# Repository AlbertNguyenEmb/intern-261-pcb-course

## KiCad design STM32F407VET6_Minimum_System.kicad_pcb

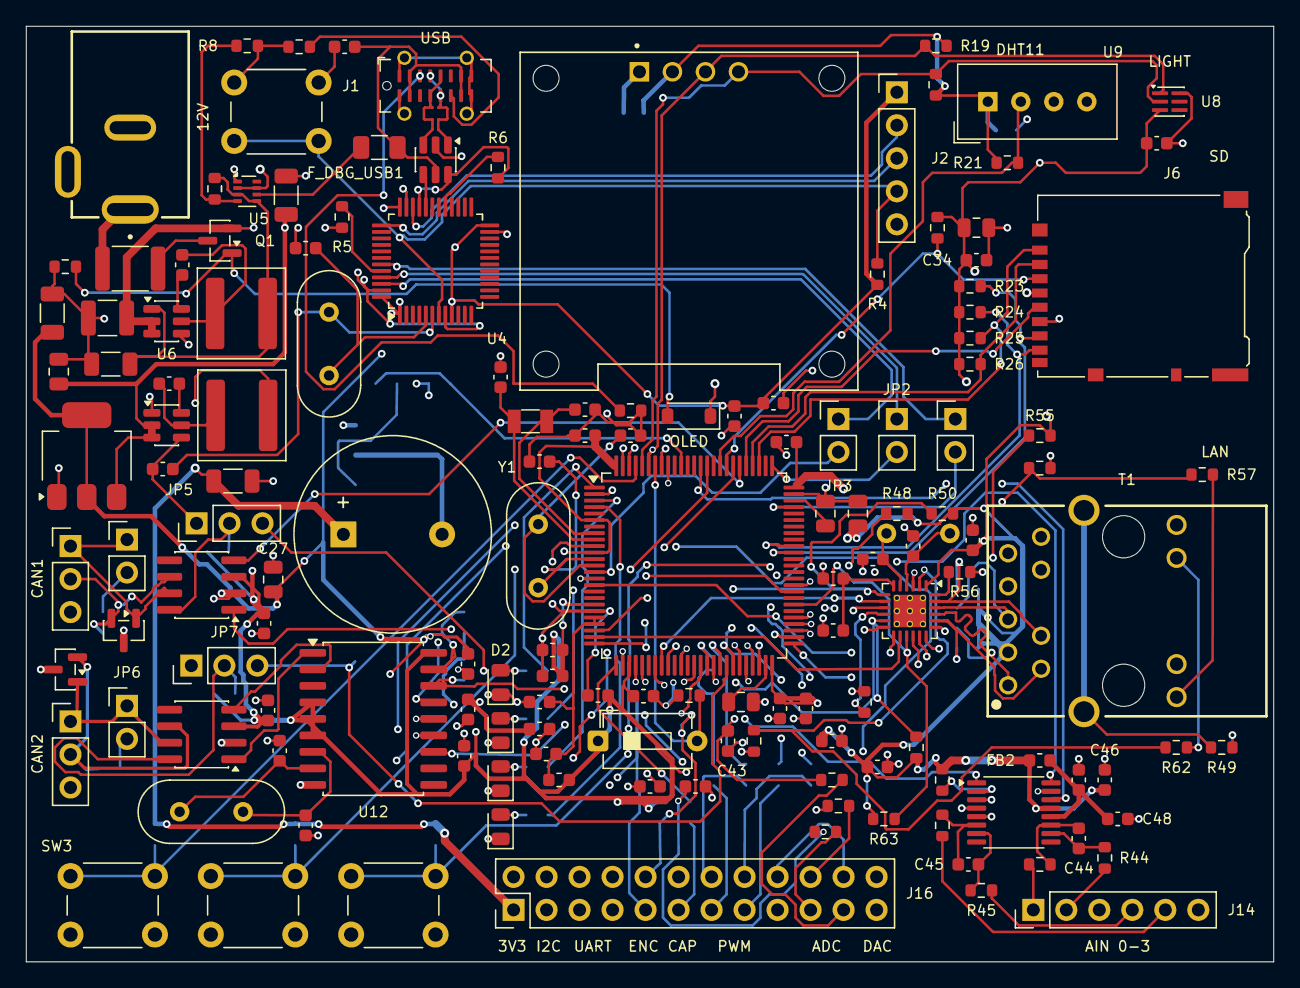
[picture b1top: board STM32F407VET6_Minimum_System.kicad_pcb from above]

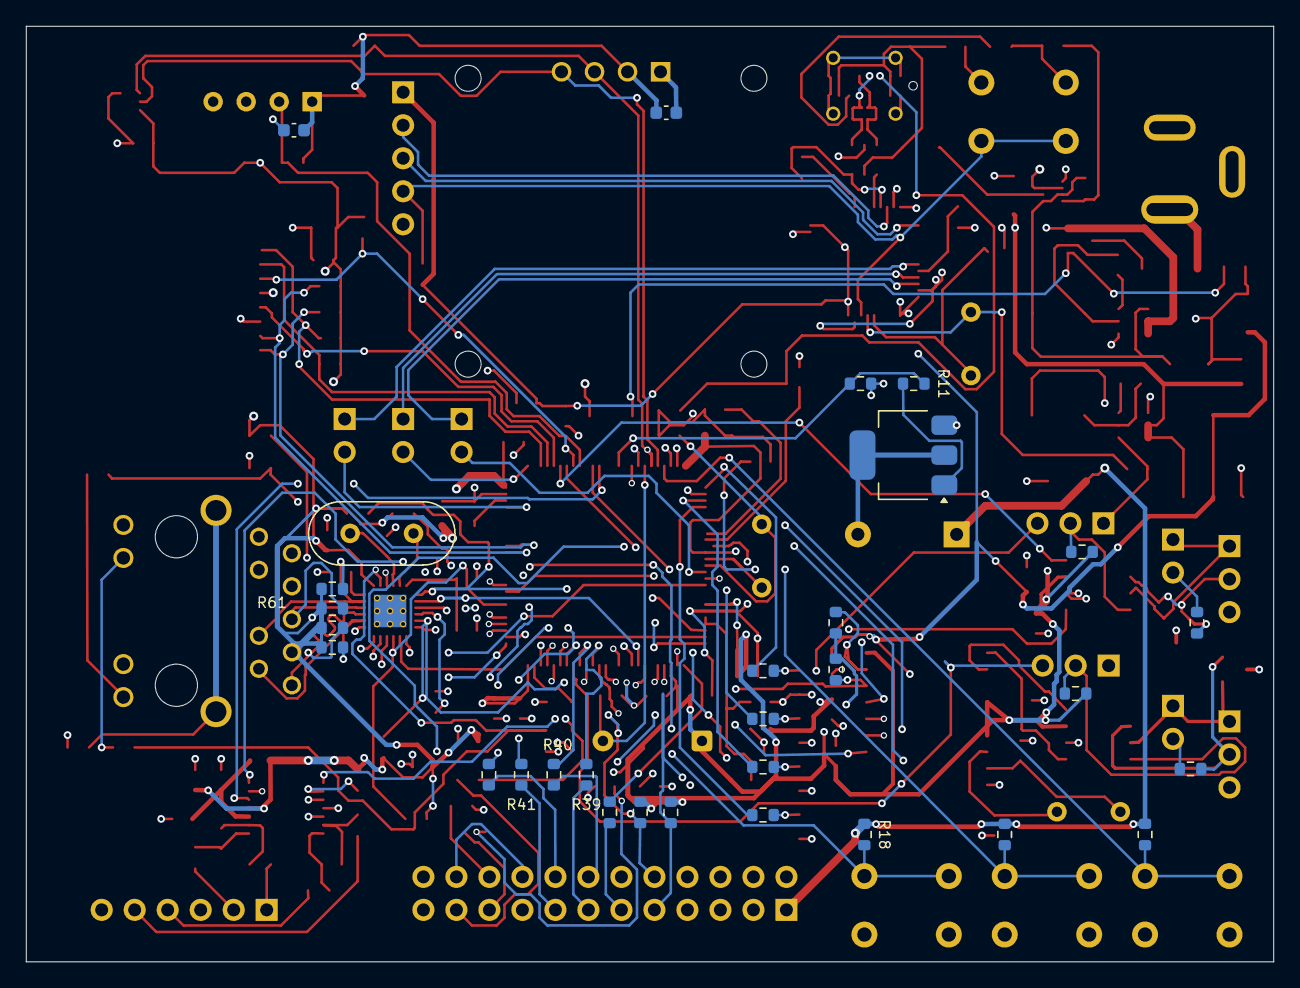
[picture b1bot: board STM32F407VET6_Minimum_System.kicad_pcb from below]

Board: 4 copper layers, 96.0 x 72.0 mm, 179 parts (30 on the bottom side), 145 nets.

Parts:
BZ1: Buzzer; Buzzer_15x7.5RM7.6
C1, C3, C36, C38, C49, C52: 18pF; C_0603_1608Metric
C2, C4: 10pF; C_0603_1608Metric
C5, C6: 2.2uF; C_0805_2012Metric
C7, C8, C9, C10, C11, C12, C13, C15, C21, C22, C23, C24, C26, C30, C31, C34, C37, C39, C40, C46, C47, C50, C51, C53: 100nF; C_0603_1608Metric
C14, C25, C48, C54, C56: 1uF; C_0603_1608Metric
C16, C18, C27, C35: 10uF; C_0805_2012Metric
C17, C19: 22pF; C_0603_1608Metric
C20, C28, C32, C33: 22uF; C_1206_3216Metric
C29: 22uF; C_1210_3225Metric
C41, C42, C43, C44, C45: 10nF; C_0603_1608Metric
C55: 470pF; C_0603_1608Metric
C_DHT1: 100nF; C_0603_1608Metric
C_LIGHT1: 1µF; C_0603_1608Metric
C_OLED1: 100nF; C_0603_1608Metric
D1: 8.2V; D_SOD-123
D2, D3, D4, D5: LED; LED_0805_2012Metric
D6, D7: PESD2CAN; SOT-23
F1: Polyfuse; Fuse_1812_4532Metric
FB1: 600R@100MHz; L_0603_1608Metric
FB2: FerriteBead; L_0603_1608Metric
F_DBG_USB1: Ihold ≈ 500mA; Fuse_1206_3216Metric
J1: USB_C_Receptacle_USB2.0_16P; USB_C_Receptacle_G-Switch_GT-USB-7051x
J2: Conn_01x05; PinHeader_1x05_P2.54mm_Vertical
J3: DC-JACK; GCT_DCJ200-10-A-XX-K_REVA
J6: Micro_SD_Card_Det2; microSD_HC_Hirose_DM3AT-SF-PEJM5
J7, J8: Conn_01x03; PinHeader_1x03_P2.54mm_Vertical
J14: Conn_01x06; PinHeader_1x06_P2.54mm_Vertical
J16: EXPANSION_2x12; PinHeader_2x12_P2.54mm_Vertical
JP1, JP2, JP3, JP4, JP6: Jumper_2_Open; PinHeader_1x02_P2.54mm_Vertical
JP5, JP7: Jumper_3_Open; PinHeader_1x03_P2.54mm_Vertical
L1: 4.7uH; L_Coilcraft_XAL6030-XXX
L2: 3.9uH; L_Coilcraft_XAL6030-XXX
Q1: AO3401A; SOT-23
Q2: BUK9832-55A; SOT-223-3_TabPin2
R1, R4, R5, R8, R16, R17, R18, R28, R30, R37, R38, R47: 10K; R_0603_1608Metric
R2, R3: 5.1K; R_0603_1608Metric
R6: 1.5K; R_0603_1608Metric
R7: 35K; R_0603_1608Metric
R9, R10: 100K; R_0603_1608Metric
R11: 100; R_0603_1608Metric
R12, R13, R14, R15, R33, R34, R35, R36, R43, R44, R45, R46: 1K; R_0603_1608Metric
R19, R20, R21: 4.7K; R_0603_1608Metric
R22, R23, R24, R25, R26, R29, R31: 47K; R_0603_1608Metric
R27, R32: 120; R_0603_1608Metric
R39, R40, R41, R42: 47; R_0603_1608Metric
R48, R50, R51, R52, R53, R54, R63: 10k; R_0603_1608Metric
R49: 0; R_0603_1608Metric
R55: 2.2k; R_0603_1608Metric
R56: 12.1k 1%; R_0603_1608Metric
R57, R62: 330; R_0603_1608Metric
R58, R59, R60, R61: 49.9 1%; R_0603_1608Metric
SW1: SW_DIP_x01; SW_DIP_SPSTx01_Slide_6.7x4.1mm_W7.62mm_P2.54mm_LowProfile
SW2, SW3, SW4, SW5: SW_Push; SW_PUSH_6mm
T1: WE-RJ45_7499410213; 7499410213
U1: STM32F407VET; LQFP-100_14x14mm_P0.5mm
U2: AMS1117-3.3; SOT-223-3_TabPin2
U3: USBLC6-2SC6; SOT-23-6
U4: STM32F103C8Tx; LQFP-48_7x7mm_P0.5mm
U5: TPS2116DRL; SOT-583-8
U6: AP63205WU; TSOT-23-6
U7: AP63203WU; TSOT-23-6
U8: APDS-9306-065; Broadcom_DFN-6_2x2mm_P0.65mm
U9: DHT11; Aosong_DHT11_5.5x12.0_P2.54mm
U10: DM-OLED096-636
U11, U13: SN65HVD230; SOIC-8_3.9x4.9mm_P1.27mm
U12: MCP2515-xSO; SOIC-18W_7.5x11.6mm_P1.27mm
U14: ADS1220xPW; TSSOP-16_4.4x5mm_P0.65mm
U15: LAN8720A; VQFN-24-1EP_4x4mm_P0.5mm_EP2.5x2.5mm_ThermalVias_Drill0.30mm
Y1, Y3: 8MHz; Crystal_HC49-4H_Vertical
Y2: 32.768kHz; Crystal_SMD_3215-2Pin_3.2x1.5mm
Y4: 16MHz; Crystal_HC49-4H_Vertical
Y5: 25MHz; Crystal_HC49-4H_Vertical

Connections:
+3V3: BZ1.1 (+), C7.2, C8.1, C9.1, C10.1, C12.1, C13.1, C15.1, C16.1, C33.2, C34.1, C35.1, C37.1, C39.1, C40.1, C46.1, C50.1, C51.1, C53.1, C56.1, C_DHT1.1, C_LIGHT1.1, C_OLED1.1, FB1.1, FB2.1, J6.4 (VDD), J16.1, L2.2, R16.1, R17.1, R18.1, R19.1, R20.1, R21.1, R22.1, R23.1, R24.1, R25.1, R26.1, R28.1, R29.1, R30.2, R31.1, R37.1, R38.1, R47.1, R48.1, R50.1, R51.1, R55.1, R58.1, R59.1, R60.1, R61.1, R63.1, SW1.1, T1.3 (CTD), U1.6 (VBAT), U1.11 (VDD), U1.19 (VDD), U1.28 (VDD), U1.50 (VDD), U1.75 (VDD), U1.100 (VDD), U7.1 (FB), U8.3 (VDD), U9.1 (VDD), U10.2 (VCC_IN), U11.3 (VCC), U12.4 (~TX0RTS), U12.5 (~TX1RTS), U12.6 (~TX2RTS), U12.18 (VDD), U13.3 (VCC), U14.13 (DVDD), U15.1 (VDD2A), U15.9 (VDDIO), U15.19 (VDD1A)
+3V3_DBG: C20.1, C22.1, C23.1, C24.1, C25.1, C26.1, C27.1, J2.1, R4.1, U2.2 (VO), U4.1 (VBAT), U4.9 (VDDA), U4.24 (VDD), U4.36 (VDD), U4.48 (VDD)
+5V_DBG_USB: F_DBG_USB1.2, U5.6 (VIN2)
+5V_SYS: C18.1, C28.1, U2.3 (VI), U5.2 (VOUT), U5.7 (VOUT), U7.2 (EN), U7.3 (IN)
/CAN_Communication/CAN1_N: D6.2, J7.2, R27.2, U11.6 (CANL)
/CAN_Communication/CAN1_P: D6.1, J7.1, JP4.1 (A), U11.7 (CANH)
/CAN_Communication/CAN2_STB: JP7.2 (C), R31.2, U13.8 (Rs)
/CAN_Communication/CAN_EXT_N: D7.2, J8.2, R32.2, U13.6 (CANL)
/CAN_Communication/CAN_EXT_P: D7.1, J8.1, JP6.1 (A), U13.7 (CANH)
/CAN_Communication/CAN_STB: JP5.2 (C), R29.2, U11.8 (Rs)
/CAN_Communication/OSC1: C36.1, U12.8 (OSC1), Y4.1
/CAN_Communication/OSC2: C38.1, U12.7 (OSC2), Y4.2
/STM32F407VET6_Minimum_System/+3V3_A: C11.1, C14.1, FB1.2, U1.21 (VREF+), U1.22 (VDDA)
/STM32F407VET6_Minimum_System/BOOT0: R1.1, SW1.2, U1.94 (BOOT0)
/STM32F407VET6_Minimum_System/LSE_1: C2.1, U1.8 (PC14), Y2.1
/STM32F407VET6_Minimum_System/LSE_2: C4.1, U1.9 (PC15), Y2.2
/STM32F407VET6_Minimum_System/PH0: C1.1, U1.12 (PH0), Y1.1
/STM32F407VET6_Minimum_System/PH1: C3.1, U1.13 (PH1), Y1.2
/analog_timer/HDR_CAPTURE: J16.11, R34.1
/analog_timer/HDR_PWM1: J16.13, R39.1
/analog_timer/HDR_PWM2: J16.14, R40.1
/analog_timer/HDR_PWM3: J16.15, R41.1
/analog_timer/HDR_PWM4: J16.16, R42.1
/analog_timer/J_ADC1: J16.19, R35.1
/analog_timer/J_ADC2: J16.20, R33.1
/analog_timer/J_ADC3: J16.21, R36.1
/ethernet/CHASSIS_GND: R49.1, T1.S1 (SHIELD1), T1.S2 (SHIELD2)
/ethernet/MDI_RX_N: R61.2, T1.5 (RD-), U15.22 (RXN)
/ethernet/MDI_RX_P: R60.2, T1.4 (RD+), U15.23 (RXP)
/ethernet/MDI_TX_N: R59.2, T1.2 (TD-), U15.20 (TXN)
/ethernet/MDI_TX_P: R58.2, T1.1 (TD+), U15.21 (TXP)
/ethernet/PHYAD0: R54.1, U15.10 (RXER/PHYAD0)
/ethernet/PHY_LED1: R53.1, R57.2, U15.3 (LED1/REGOFF)
/ethernet/PHY_LED2: R52.1, R62.2, U15.2 (LED2/~INTSEL)
/ethernet/PHY_RBIAS: R56.1, U15.24 (RBIAS)
/ethernet/XTAL1: C49.1, U15.5 (XTAL1/CLKIN), Y5.1
/ethernet/XTAL2: C52.1, U15.4 (XTAL2), Y5.2
/onboard_debugger/DBG_MCU_USB_N: U3.4 (I/O2), U4.32 (PA11)
/onboard_debugger/DBG_MCU_USB_P: R6.1, U3.6 (I/O1), U4.33 (PA12)
/onboard_debugger/F103_NRST: J2.4, R4.2, SW2.2, U4.7 (NRST)
/onboard_debugger/F103_SWCLK: J2.3, U4.37 (PA14)
/onboard_debugger/F103_SWDIO: J2.2, U4.34 (PA13)
/onboard_debugger/PH0_DBG: C17.1, U4.5 (PD0), Y3.1
/onboard_debugger/PH1_DBG: C19.1, U4.6 (PD1), Y3.2
/onboard_debugger/TGT_NRST_DRV: JP3.1 (A), U4.46 (PB9)
/onboard_debugger/TGT_SWCLK_DRV: JP2.1 (A), U4.45 (PB8)
/onboard_debugger/TGT_SWDIO_DRV: JP1.1 (A), U4.43 (PB7)
/onboard_debugger/VBUS_DBG_RAW: C21.2, F_DBG_USB1.1, J1.A4 (VBUS), J1.A9 (VBUS), J1.B4 (VBUS), J1.B9 (VBUS), U3.5 (VBUS)
/power_supply/+5V_EXT: C32.1, L1.2, R7.1, U5.3 (VIN1), U5.5 (MODE), U6.1 (FB)
/power_supply/+12V: F1.1, J3.1
/power_supply/+12V_PROT: C29.1, D1.1 (K), Q1.2 (S), U6.2 (EN), U6.3 (IN)
/power_supply/PR1: R7.2, R8.1, U5.4 (PR1)
/precision_ADC/ADC_AVDD: C47.1, C48.1, FB2.2, U14.12 (AVDD)
/precision_ADC/ADC_EXT_AIN0: C44.1, R43.2, U14.11 (AIN0/REFP1)
/precision_ADC/ADC_EXT_AIN1: C44.2, R44.2, U14.10 (AIN1)
/precision_ADC/ADC_EXT_AIN2: C45.1, R45.2, U14.7 (AIN2)
/precision_ADC/ADC_EXT_AIN3: C45.2, R46.2, U14.6 (AIN3/REFN1)
/precision_ADC/J_AIN0: J14.1, R43.1
/precision_ADC/J_AIN1: J14.2, R44.1
/precision_ADC/J_AIN2: J14.4, R45.1
/precision_ADC/J_AIN3: J14.5, R46.1
ADC_EXT_CS_N: R47.2, U1.41 (PE10), U14.2 (~CS)
ADC_EXT_DRDY_N: U1.87 (PD6), U14.14 (~DRDY)
ADC_IN0: C42.1, R35.2, U1.23 (PA0)
ADC_IN9: C43.1, R36.2, U1.36 (PB1)
ADC_IN10: C41.1, R33.2, U1.15 (PC0)
CAN1_RS: JP5.3 (B), U1.39 (PE8)
CAN1_RX: U1.81 (PD0), U11.4 (R)
CAN1_TX: U1.82 (PD1), U11.1 (D)
CAN_EXT_CS_N: R28.2, U1.38 (PE7), U12.16 (~CS)
CAN_EXT_INT_N: U1.55 (PD8), U12.12 (~INT)
CAN_EXT_RESET_N: R30.1, U1.86 (PD5), U12.17 (~RESET)
CAN_EXT_RS: JP7.3 (B), U1.43 (PE12)
CAN_EXT_RX: U12.2 (RXCAN), U13.4 (R)
CAN_EXT_TX: U12.1 (TXCAN), U13.1 (D)
DAC_OUT1: J16.23, U1.29 (PA4)
DAC_OUT2: J16.24, U1.30 (PA5)
DBG_USB_D_N: J1.A7 (D-), J1.B7 (D-), U3.3 (I/O2)
DBG_USB_D_P: J1.A6 (D+), J1.B6 (D+), U3.1 (I/O1)
DHT_DATA: R21.2, U1.84 (PD3), U9.2 (DATA)
ETH_CRS_DV: R51.2, U1.32 (PA7), U15.11 (CRS_DV/MODE2)
ETH_MDC: U1.16 (PC1), U15.13 (MDC)
ETH_MDIO: R55.2, U1.25 (PA2), U15.12 (MDIO)
ETH_REF_CLK: U1.24 (PA1), U15.14 (~INT/REFCLKO)
ETH_RESET_N: R63.2, U1.57 (PD10), U15.15 (~RST)
ETH_RXD0: R48.2, U1.33 (PC4), U15.8 (RXD0/MODE0)
ETH_RXD1: R50.2, U1.34 (PC5), U15.7 (RXD1/MODE1)
ETH_TXD0: U1.51 (PB12), U15.17 (TXD0)
ETH_TXD1: U1.52 (PB13), U15.18 (TXD1)
ETH_TX_EN: U1.48 (PB11), U15.16 (TXEN)
GND: C1.2, C2.2, C3.2, C4.2, C5.1, C6.1, C7.1, C8.2, C9.2, C10.2, C11.2, C12.2, C13.2, C14.2, C15.2, C16.2, C17.2, C18.2, C19.2, C20.2, C21.1, C22.2, C23.2, C24.2, C25.2, C26.2, C27.2, C28.2, C29.2, C32.2, C33.1, C34.2, C35.2, C36.2, C37.2, C38.2, C39.2, C40.2, C41.2, C42.2, C43.2, C46.2, C47.2, C48.2, C49.2, C50.2, C51.2, C52.2, C53.2, C54.2, C55.2, C56.2, C_DHT1.2, C_LIGHT1.2, C_OLED1.2, D2.1 (K), D3.1 (K), D4.1 (K), D5.1 (K), D6.3, D7.3, J1.A1 (GND), J1.A12 (GND), J1.B1 (GND), J1.B12 (GND), J1.SH (SHIELD), J2.5, J3.2, J6.6 (VSS), J7.3, J8.3, J14.3, J14.6, J16.2, J16.7, J16.8, J16.12, J16.17, J16.18, J16.22, JP5.1 (A), JP7.1 (A), Q2.3 (S), R1.2, R2.2, R3.2, R5.1, R8.2, R9.2, R10.1, R49.2, R52.2, R53.2, R54.2, R56.2, SW2.1, SW3.2, SW4.2, SW5.2, T1.12, T1.14, U1.10 (VSS), U1.20 (VSSA), U1.27 (VSS), U1.74 (VSS), U1.99 (VSS), U2.1 (GND), U3.2 (GND), U4.8 (VSSA), U4.23 (VSS), U4.35 (VSS), U4.47 (VSS), U5.1 (GND), U6.4 (GND), U7.4 (GND), U8.6 (GND), U9.4 (GND), U10.1 (GND), U11.2 (GND), U12.9 (VSS), U13.2 (GND), U14.3 (CLK), U14.4 (DGND), U14.5 (AVSS), U15.25 (VSS)
GPIO_BTN1_N: R16.2, SW3.1, U1.97 (PE0)
GPIO_BTN2_N: R17.2, SW4.1, U1.98 (PE1)
GPIO_BTN3_N: R18.2, SW5.1, U1.46 (PE15)
GPIO_LED1: R12.1, U1.1 (PE2)
GPIO_LED2: R13.1, U1.2 (PE3)
GPIO_LED3: R14.1, U1.3 (PE4)
GPIO_LED4: R15.1, U1.4 (PE5)
I2C1_SCL: J16.3, R19.2, U1.95 (PB8), U8.1 (SCL), U10.3 (SCL)
I2C1_SDA: J16.4, R20.2, U1.96 (PB9), U8.2 (SDA), U10.4 (SDA)
unnamed: BZ1.2 (-), Q2.2 (D)
unnamed: D1.2 (A), Q1.1 (G), R9.1
unnamed: D2.2 (A), R12.2
unnamed: D3.2 (A), R13.2
unnamed: D4.2 (A), R14.2
unnamed: D5.2 (A), R15.2
unnamed: J1.A5 (CC1), R3.1
unnamed: J1.B5 (CC2), R2.1
unnamed: JP4.2 (B), R27.1
unnamed: JP6.2 (B), R32.1
unnamed: F1.2, Q1.3 (D)
unnamed: Q2.1 (G), R11.2
unnamed: R57.1, T1.11
unnamed: R62.1, T1.13
unnamed: C5.2, U1.49 (VCAP_1)
unnamed: C6.2, U1.73 (VCAP_2)
unnamed: R5.2, U4.44 (BOOT0)
unnamed: R6.2, U4.29 (PA8)
unnamed: C30.1, U6.6 (BST)
unnamed: C30.2, L1.1, U6.5 (SW)
unnamed: C31.1, U7.6 (BST)
unnamed: C31.2, L2.1, U7.5 (SW)
unnamed: C54.1, C55.1, U15.6 (VDDCR)
SDIO_CK: J6.5 (CLK), U1.80 (PC12)
SDIO_CMD: J6.3 (CMD), R22.2, U1.83 (PD2)
SDIO_D0: J6.7 (DAT0), R23.2, U1.65 (PC8)
SDIO_D1: J6.8 (DAT1), R24.2, U1.66 (PC9)
SDIO_D2: J6.1 (DAT2), R25.2, U1.78 (PC10)
SDIO_D3: J6.2 (DAT3/CD), R26.2, U1.79 (PC11)
SPI2_MISO: U1.53 (PB14), U12.15 (SO), U14.15 (DOUT/~DRDY)
SPI2_MOSI: U1.54 (PB15), U12.14 (SI), U14.16 (DIN)
SPI2_SCK: U1.47 (PB10), U12.13 (SCK), U14.1 (SCLK)
TARGET_NRST: JP3.2 (B), U1.14 (NRST)
TARGET_SWCLK: JP2.2 (B), U1.76 (PA14)
TARGET_SWDIO: JP1.2 (B), U1.72 (PA13)
TIM1_CH1: R39.2, U1.40 (PE9)
TIM1_CH2: R40.2, U1.42 (PE11)
TIM1_CH3: R41.2, U1.44 (PE13)
TIM1_CH4: R42.2, U1.45 (PE14)
TIM2_CAPTURE: R34.2, U1.26 (PA3)
TIM3_BUZZER: R10.2, R11.1, U1.90 (PB4)
TIM4_ENC_A: J16.9, R37.2, U1.59 (PD12)
TIM4_ENC_B: J16.10, R38.2, U1.60 (PD13)
USART1_RX: J16.6, U1.93 (PB7)
USART1_TX: J16.5, U1.92 (PB6)
